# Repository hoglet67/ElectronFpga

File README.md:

# ElectronFpga

Inspired by [a thread on
Stardot](https://stardot.org.uk/forums/viewtopic.php?f=3&t=9223), this project
implements the Acorn Electron ULA in various FPGAs, and can emulate a full
Electron system on an FPGA eval board.

Features:
- Everything that was in the original Elk ULA (including cassette I/O)
- Turbo mode (memory access at 2MHz)
- JAFA Mode 7
- VGA output
- SD card access and MMFS

## Hardware targets

### Papilio Duo (Xilinx Spartan 6)

This can be used as a standalone Electron emulator, or with an adapter board
and some level shifters, as a ULA replacement.

### Altera DE1

This can be used as a standalone Electron emulator.

### Intel Max 10 (pcb/ folder in this repository)

This is a board designed specifically for this project, to fit inside an
Electron with its ULA replaced with turned-pin sockets.  Components:

- Intel Max 10 10M08SCU169 FPGA with 8k LUTs and 42kB block RAM.
- 32MB SDRAM
- 8+MB flash
- micro SD socket
- micro USB port
- stereo DAC for audio

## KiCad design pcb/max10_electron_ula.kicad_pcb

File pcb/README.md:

# ElectronFpga/pcb

This is a PCB for the Electron ULA replacement project (the "Ultimate Electron Upgrade").

Stardot thread:
https://stardot.org.uk/forums/viewtopic.php?f=3&t=9223

Status: v1 board sent to fab!

Pictures
--------

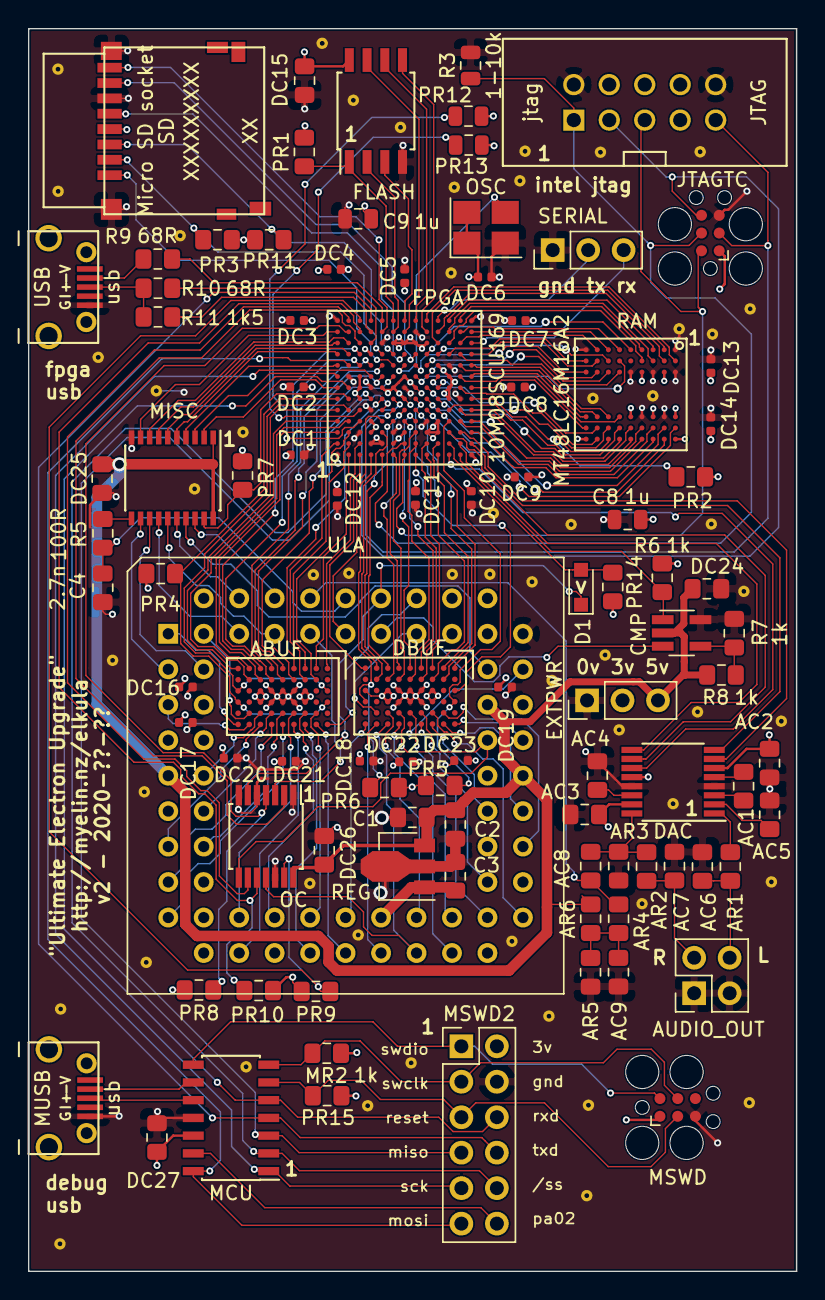
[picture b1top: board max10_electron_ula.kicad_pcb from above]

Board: 4 copper layers, 55.0 x 89.0 mm, 149 parts (0 on the bottom side), 194 nets.

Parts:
ABUF: 74LVTH162245ZRDR; ti_zrd_54_pbga
AC1, AC5: 1u; C_0805_2012Metric_Pad1.15x1.40mm_HandSolder
AC2, AC3: 4.7u; C_0805_2012Metric_Pad1.15x1.40mm_HandSolder
AC4: 2.2u; C_0805_2012Metric_Pad1.15x1.40mm_HandSolder
AC6, AC7: 2.7n NF; C_0805_2012Metric_Pad1.15x1.40mm_HandSolder
AC8, AC9: 10u; C_0805_2012Metric_Pad1.15x1.40mm_HandSolder
AR1, AR2: 560R NF; R_0805_2012Metric_Pad1.15x1.40mm_HandSolder
AR3: 10k NF; R_0805_2012Metric_Pad1.15x1.40mm_HandSolder
AR4, AR5, AR6: 10k; R_0805_2012Metric_Pad1.15x1.40mm_HandSolder
AUDIO_OUT: audio out; PinHeader_2x02_P2.54mm_Vertical
C1: 10u; C_0805_2012Metric_Pad1.15x1.40mm_HandSolder
C2, C3: 1u; C_0805_2012Metric_Pad1.15x1.40mm_HandSolder
C4: 2.7n; C_0805_2012Metric_Pad1.15x1.40mm_HandSolder
C8, C9: 1u; C_0805_2012Metric
CMP: MIC7221YM5-TR; SOT-23-5_HandSoldering
D1: BAT54; D_SOD-323_HandSoldering
DAC: WM8524CGEDT; TSSOP-16_4.4x5mm_P0.65mm
DBUF: 74LVTH162245ZRDR; ti_zrd_54_pbga
DC1, DC2, DC3, DC4, DC5, DC6, DC7, DC8, DC9, DC10, DC11, DC12, DC13, DC14, DC16, DC17, DC18, DC19, DC20, DC21, DC22, DC23: 100n; C_0402_1005Metric
DC15, DC24, DC25, DC26, DC27: 100n; C_0805_2012Metric_Pad1.15x1.40mm_HandSolder
EXTPWR: ext pwr; PinHeader_1x03_P2.54mm_Vertical
FLASH: W25Q128JVSIM; SOIJ-8_5.3x5.3mm_P1.27mm
FPGA: 10M08SCU169; intel_ubga169
JTAG: jtag; jtag_shrouded_2x5
JTAGTC: jtagtc; Tag-Connect_TC2030-IDC-FP_2x03_P1.27mm_Vertical
MCU: atsamd11c; SOIC-14_3.9x8.7mm_P1.27mm
MISC: 74HCT245PW; SSOP-20_4.4x6.5mm_P0.65mm
MR2: 1k; R_0805_2012Metric_Pad1.15x1.40mm_HandSolder
MSWD: swd; Tag-Connect_TC2030-IDC-FP_2x03_P1.27mm_Vertical
MSWD2: swd; PinHeader_2x06_P2.54mm_Vertical
MUSB: usb; micro_usb_b_smd_molex
OC: 74HCT125PW; TSSOP-14_4.4x5mm_P0.65mm
OSC: osc; Oscillator_SMD_Abracon_ASE-4Pin_3.2x2.5mm_HandSoldering
PR1, PR2, PR3, PR4, PR5, PR6, PR7, PR8, PR9, PR10, PR14, PR15: 10k; R_0805_2012Metric_Pad1.15x1.40mm_HandSolder
PR11: 10k NF; R_0805_2012Metric_Pad1.15x1.40mm_HandSolder
PR12, PR13: 10k; R_0805_2012Metric
R3: 1-10k; R_0805_2012Metric
R5: 100R; R_0805_2012Metric_Pad1.15x1.40mm_HandSolder
R6, R7, R8: 1k; R_0805_2012Metric_Pad1.15x1.40mm_HandSolder
R9, R10: 68R; R_0805_2012Metric_Pad1.15x1.40mm_HandSolder
R11: 1k5; R_0805_2012Metric_Pad1.15x1.40mm_HandSolder
RAM: MT48LC16M16A2; sdram_54tfbga
REG: AP7365-33YG-XX; SOT-89-3
SD: Micro SD socket; hirose_micro_sd_card_socket
SERIAL: fpga serial port; PinHeader_1x03_P2.54mm_Vertical
ULA: ULA header; PLCC-68_THT-Socket-Electron-ULA
USB: usb; micro_usb_b_smd_molex
staple_single1, staple_single2, staple_single3, staple_single4, staple_single5, staple_single6, staple_single7, staple_single8, staple_single9, staple_single10, staple_single11, staple_single12, staple_single13, staple_single14, staple_single15, staple_single16, staple_single17, staple_single18, staple_single19, staple_single20, staple_single21, staple_single22, staple_single23, staple_single24, staple_single25, staple_single26, staple_single27, staple_single28, staple_single29, staple_single30, staple_single31, staple_single32, staple_single33, staple_single34, staple_single35, staple_single36, staple_single37, staple_single38, staple_single39, staple_single40, staple_single41, staple_single42, staple_single43, staple_single44, staple_single45, staple_single46, staple_single47, staple_single48, staple_single49, staple_single50, staple_single51, staple_single52, staple_single53: via_single

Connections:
3V3: ABUF.C3, ABUF.C4, ABUF.G3, ABUF.G4, AC2.1, AC3.1, C3.1, C8.1, C9.1, DAC.6, DAC.12, DAC.15, DBUF.C3, DBUF.C4, DBUF.G3, DBUF.G4, DBUF.J3, DC1.1, DC2.1, DC3.1, DC4.1, DC5.1, DC6.1, DC7.1, DC8.1, DC9.1, DC10.1, DC11.1, DC12.1, DC13.1, DC14.1, DC15.1, DC16.2, DC17.2, DC18.2, DC19.2, DC20.2, DC21.2, DC22.2, DC23.2, DC27.2, EXTPWR.2, FLASH.8, FPGA.C6, FPGA.C7, FPGA.C8, FPGA.D3, FPGA.D4, FPGA.D10, FPGA.E7, FPGA.F2, FPGA.F7, FPGA.F11, FPGA.G3, FPGA.G6, FPGA.G8, FPGA.G11, FPGA.H7, FPGA.H11, FPGA.J3, FPGA.J11, FPGA.K3, FPGA.K4, FPGA.K9, FPGA.L6, FPGA.L7, FPGA.L8, JTAG.4, JTAGTC.1, MCU.12, MR2.2, MSWD.1, MSWD2.2, OSC.1, OSC.4, PR1.2, PR2.2, PR3.2, PR4.2, PR5.2, PR6.2, PR7.2, PR8.2, PR9.2, PR10.2, PR11.1, PR12.2, PR13.2, PR14.1, PR15.2, R6.2, RAM.A7, RAM.A9, RAM.B3, RAM.C7, RAM.D3, RAM.E7, RAM.J9, REG.1, SD.4, ULA.6, ULA.7, ULA.8, ULA.11, ULA.16, ULA.18, ULA.19, ULA.22, ULA.29, ULA.52, ULA.53
5V: AR6.2, C1.2, C2.2, CMP.2, DC24.2, DC25.2, DC26.1, EXTPWR.3, MISC.1, MISC.20, OC.14, R8.2, REG.3, ULA.9, ULA.43, ULA.48
A0_5V: ABUF.H6, ULA.5
A1_5V: ABUF.J6, ULA.1
A2_5V: ABUF.F5, ULA.12
A3_5V: ABUF.C6, ULA.24
A4_5V: ABUF.D5, ULA.21
A5_5V: ABUF.D6, ULA.20
A6_5V: ABUF.E6, ULA.17
A7_5V: ABUF.F6, ULA.15
A8_5V: ABUF.H5, ULA.2
A9_5V: ABUF.B6, ULA.26
A10_5V: ABUF.B5, ULA.25
A11_5V: ABUF.C5, ULA.23
A12_5V: ABUF.G6, ULA.13
A13_5V: ABUF.E5, ULA.14
A14_5V: ABUF.G5, ULA.10
A15_5V: ABUF.A6, ULA.56
A_buf_DIR: ABUF.A3, ABUF.J3, FPGA.B5
A_buf_nOE: ABUF.A4, ABUF.J4, FPGA.A6, PR4.1
CAPS_LOCK_5V: OC.3, ULA.63
CAS_IN_5V: CMP.3, ULA.59
CAS_IN_divider: CMP.4, R7.2, R8.1
CAS_MO_5V: MISC.18, ULA.64
CAS_OUT_5V: MISC.17, ULA.50
D_buf_DIR: DBUF.A3, FPGA.H1
D_buf_nOE: DBUF.A4, FPGA.L4, PR5.1
GND: ABUF.D3, ABUF.D4, ABUF.E3, ABUF.E4, ABUF.F3, ABUF.F4, AC1.2, AC2.2, AC3.2, AC4.2, AC6.2, AC7.2, AC9.2, AR3.2, AR5.2, AUDIO_OUT.1, AUDIO_OUT.3, C1.1, C2.1, C3.2, C4.2, C8.2, C9.2, CMP.5, DAC.4, DAC.13, DBUF.D3, DBUF.D4, DBUF.E3, DBUF.E4, DBUF.F3, DBUF.F4, DC1.2, DC2.2, DC3.2, DC4.2, DC5.2, DC6.2, DC7.2, DC8.2, DC9.2, DC10.2, DC11.2, DC12.2, DC13.2, DC14.2, DC15.2, DC16.1, DC17.1, DC18.1, DC19.1, DC20.1, DC21.1, DC22.1, DC23.1, DC24.1, DC25.1, DC26.2, DC27.1, EXTPWR.1, FLASH.4, FPGA.A1, FPGA.A13, FPGA.B8, FPGA.C3, FPGA.D2, FPGA.D5, FPGA.D7, FPGA.E2, FPGA.E11, FPGA.F3, FPGA.G7, FPGA.H12, FPGA.J4, FPGA.L9, FPGA.M6, FPGA.N1, FPGA.N13, JTAG.2, JTAG.10, JTAGTC.5, MCU.11, MISC.10, MSWD.5, MSWD2.4, MUSB.5, OC.1, OC.5, OC.7, OC.12, OSC.2, R3.2, R7.1, RAM.A1, RAM.A3, RAM.B7, RAM.C3, RAM.D7, RAM.E3, RAM.J1, REG.2, SD.6, SD.SH1, SD.SH2, SERIAL.1, ULA.51, ULA.68, USB.5, staple_single1.1, staple_single2.1, staple_single3.1, staple_single4.1, staple_single5.1, staple_single6.1, staple_single7.1, staple_single8.1, staple_single9.1, staple_single10.1, staple_single11.1, staple_single12.1, staple_single13.1, staple_single14.1, staple_single15.1, staple_single16.1, staple_single17.1, staple_single18.1, staple_single19.1, staple_single20.1, staple_single21.1, staple_single22.1, staple_single23.1, staple_single24.1, staple_single25.1, staple_single26.1, staple_single27.1, staple_single28.1, staple_single29.1, staple_single30.1, staple_single31.1, staple_single32.1, staple_single33.1, staple_single34.1, staple_single35.1, staple_single36.1, staple_single37.1, staple_single38.1, staple_single39.1, staple_single40.1, staple_single41.1, staple_single42.1, staple_single43.1, staple_single44.1, staple_single45.1, staple_single46.1, staple_single47.1, staple_single48.1, staple_single49.1, staple_single50.1, staple_single51.1, staple_single52.1, staple_single53.1
HS_n: FPGA.B10, MISC.6
IRQ_n_in: DBUF.G1, FPGA.E1
IRQ_n_out: FPGA.C13, OC.13, PR9.1
KBD0_5V: DBUF.J6, ULA.27
KBD1_5V: DBUF.H6, ULA.28
KBD2_5V: DBUF.G5, ULA.31
KBD3_5V: DBUF.F6, ULA.32
NMI_n_in: DBUF.H2, FPGA.F4
PD0_5V: DBUF.E5, ULA.33
PD1_5V: DBUF.C5, ULA.35
PD2_5V: DBUF.D6, ULA.36
PD3_5V: DBUF.D5, ULA.38
PD4_5V: DBUF.B5, ULA.39
PD5_5V: DBUF.B6, ULA.41
PD6_5V: DBUF.C6, ULA.42
PD7_5V: DBUF.A6, ULA.45
PHI_OUT_5V: C4.1, R5.2, ULA.60
PHI_OUT_5V_prefilter: MISC.11, R5.1
ROM_n: FPGA.E4, ULA.61
RST_n_in: D1.2, FPGA.L2, PR14.2
RST_n_out: FPGA.B12, OC.4, PR8.1
RnW_5V: DBUF.F5, OC.8, ULA.46
RnW_in: DBUF.F2, FPGA.H3
RnW_nOE: FPGA.C12, OC.10, PR10.1
RnW_out: FPGA.B13, OC.9
SOUND_OUT_5V: AC8.2, AR4.1, ULA.62
USBDM: R9.1, USB.2
USBDP: R10.1, R11.1, USB.3
USB_M: FPGA.E13, R9.2
USB_P: FPGA.D11, R10.2
USB_PU: FPGA.D12, R11.2
addr0: ABUF.H1, FPGA.B4
addr1: ABUF.J1, FPGA.A5
addr2: ABUF.F2, FPGA.C9
addr3: ABUF.C1, FPGA.B3
addr4: ABUF.D2, FPGA.F8
addr5: ABUF.D1, FPGA.E6
addr6: ABUF.E1, FPGA.E8
addr7: ABUF.F1, FPGA.D9
addr8: ABUF.H2, FPGA.A4
addr9: ABUF.B1, FPGA.B1
addr10: ABUF.B2, FPGA.B2
addr11: ABUF.C2, FPGA.A2
addr12: ABUF.G1, FPGA.C10
addr13: ABUF.E2, FPGA.E9
addr14: ABUF.G2, FPGA.A3
addr15: ABUF.A1, FPGA.C2
audio_bias: AC9.1, AR4.2, AR5.1, AR6.1
audio_out_left: AC6.1, AR1.2, AUDIO_OUT.4
audio_out_right: AC7.1, AR2.2, AUDIO_OUT.2
blue: FPGA.A9, MISC.4
blue_5V: MISC.16, ULA.66
caps: FPGA.C11, OC.2
casIn: CMP.1, FPGA.M1, R6.1
casMO: FPGA.A7, MISC.2
casOut: FPGA.A8, MISC.3
clk_in: DBUF.E1, FPGA.H4
clk_in_5V: DBUF.E6, ULA.49
clk_osc: FPGA.G9, OSC.3
clk_out: FPGA.A12, MISC.9
csync: FPGA.A10, MISC.5
csync_5V: MISC.15, ULA.65
dac_bclk: DAC.9, FPGA.M2
dac_dacdat: DAC.7, FPGA.M3
dac_lrclk: DAC.8, FPGA.N2
dac_mclk: DAC.10, FPGA.L3
dac_nmute: DAC.11, FPGA.L1
dac_out_left: AR1.1, DAC.1
dac_out_right: AC8.1, AR2.1, AR3.1, DAC.16
dac_power_cpca: AC5.1, DAC.5
dac_power_cpcb: AC5.2, DAC.3
dac_power_cpvoutn: AC1.1, DAC.2
dac_power_vmid: AC4.1, DAC.14
data0: DBUF.E2, FPGA.H2
data1: DBUF.C2, FPGA.H6
data2: DBUF.D1, FPGA.G4
data3: DBUF.D2, FPGA.J2
data4: DBUF.B2, FPGA.H5
data5: DBUF.B1, FPGA.K2
data6: DBUF.C1, FPGA.J1
data7: DBUF.A1, FPGA.K1
flash_IO0: FLASH.5, FPGA.J12
flash_IO1: FLASH.2, FPGA.F12
flash_IO2: FLASH.3, FPGA.G13
flash_IO3: FLASH.7, FPGA.G12
flash_SCK: FLASH.6, FPGA.H13
flash_nCE: FLASH.1, FPGA.F13, PR1.1
fpga_CONF_DONE: FPGA.C5, PR12.1
fpga_TCK: FPGA.G2, JTAG.1, JTAGTC.4, R3.1
fpga_TDI: FPGA.F5, JTAG.9, JTAGTC.3
fpga_TDO: FPGA.F6, JTAG.3, JTAGTC.6
fpga_TMS: FPGA.G1, JTAG.5, JTAGTC.2
fpga_nSTATUS: FPGA.C4, PR13.1
green: FPGA.A11, MISC.7
green_5V: MISC.13, ULA.4
input_buf_nOE: DBUF.J4, FPGA.D1, PR6.1
kbd0: DBUF.J1, FPGA.C1
kbd1: DBUF.H1, FPGA.E3
kbd2: DBUF.G2, FPGA.G5
kbd3: DBUF.F1, FPGA.F1
mcu_MISO: FPGA.E5, MCU.3, MSWD2.7
mcu_MOSI: FPGA.B9, MCU.14, MSWD2.11
mcu_PA02: MCU.13, MSWD2.12
mcu_RESET: MCU.6, MSWD.3, MSWD2.5, PR15.1
mcu_SCK: FPGA.D8, MCU.1, MSWD2.9
mcu_SS: FPGA.D6, MCU.2, MSWD2.10
mcu_SWCLK: MCU.7, MR2.1, MSWD.4, MSWD2.3
mcu_SWDIO: MCU.8, MSWD.2, MSWD2.1
mcu_USBDM: MCU.9, MUSB.2
mcu_USBDP: MCU.10, MUSB.3
mcu_debug_RXD: FPGA.B7, MCU.5, MSWD2.6
mcu_debug_TXD: FPGA.D13, MCU.4, MSWD2.8
misc_buf_nOE: FPGA.B6, MISC.19, PR7.1
nHS_5V: MISC.14, ULA.67
nIRQ_5V: DBUF.G6, OC.11, ULA.30
nNMI_5V: DBUF.H5, ULA.57
nRESET_5V: D1.1, OC.6, ULA.58
red: FPGA.B11, MISC.8
red_5V: MISC.12, ULA.3
sd_CLK_SCK: FPGA.G10, SD.5
sd_CMD_MOSI: FPGA.F10, PR11.2, SD.3
sd_DAT0_MISO: FPGA.H10, SD.7
sd_DAT1: FPGA.E12, SD.8
sd_DAT2: FPGA.F9, SD.1
sd_DAT3_nCS: FPGA.E10, PR3.1, SD.2
sdram_A0: FPGA.M9, RAM.H7
sdram_A1: FPGA.K7, RAM.H8
sdram_A2: FPGA.N7, RAM.J8
sdram_A3: FPGA.N8, RAM.J7
sdram_A4: FPGA.H9, RAM.J3
sdram_A5: FPGA.L10, RAM.J2
sdram_A6: FPGA.J9, RAM.H3
sdram_A7: FPGA.N10, RAM.H2
sdram_A8: FPGA.M11, RAM.H1
sdram_A9: FPGA.J8, RAM.G3
sdram_A10: FPGA.M7, RAM.H9
sdram_A11: FPGA.K10, RAM.G2
sdram_A12: FPGA.N12, RAM.G1
sdram_BA0: FPGA.N9, RAM.G7
sdram_BA1: FPGA.K8, RAM.G8
sdram_CKE: FPGA.M10, RAM.F3
sdram_CLK: FPGA.H8, RAM.F2
sdram_DQ0: FPGA.J5, RAM.A8
sdram_DQ1: FPGA.K5, RAM.B9
sdram_DQ2: FPGA.J6, RAM.B8
sdram_DQ3: FPGA.N3, RAM.C9
sdram_DQ4: FPGA.M4, RAM.C8
sdram_DQ5: FPGA.N4, RAM.D9
sdram_DQ6: FPGA.K6, RAM.D8
sdram_DQ7: FPGA.M5, RAM.E9
sdram_DQ8: FPGA.J10, RAM.E1
sdram_DQ9: FPGA.L11, RAM.D2
sdram_DQ10: FPGA.M13, RAM.D1
sdram_DQ11: FPGA.L12, RAM.C2
sdram_DQ12: FPGA.L13, RAM.C1
sdram_DQ13: FPGA.K12, RAM.B2
sdram_DQ14: FPGA.K11, RAM.B1
sdram_DQ15: FPGA.J13, RAM.A2
sdram_LDQM: FPGA.N5, RAM.E8
sdram_UDQM: FPGA.M12, RAM.F1
sdram_nCAS: FPGA.M8, RAM.F7
sdram_nCS: FPGA.N6, PR2.1, RAM.G9
sdram_nRAS: FPGA.L5, RAM.F8
sdram_nWE: FPGA.J7, RAM.F9
serial_RXD: FPGA.N11, SERIAL.3
serial_TXD: FPGA.K13, SERIAL.2

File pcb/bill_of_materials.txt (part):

Identifier	Value	Description	KiCad package
DC1	100n	Capacitor 0402: 100n	Capacitor_SMD:C_0402_1005Metric
DC10	100n	Capacitor 0402: 100n	Capacitor_SMD:C_0402_1005Metric
DC11	100n	Capacitor 0402: 100n	Capacitor_SMD:C_0402_1005Metric
DC12	100n	Capacitor 0402: 100n	Capacitor_SMD:C_0402_1005Metric
DC13	100n	Capacitor 0402: 100n	Capacitor_SMD:C_0402_1005Metric
DC14	100n	Capacitor 0402: 100n	Capacitor_SMD:C_0402_1005Metric
DC16	100n	Capacitor 0402: 100n	Capacitor_SMD:C_0402_1005Metric
DC17	100n	Capacitor 0402: 100n	Capacitor_SMD:C_0402_1005Metric
DC18	100n	Capacitor 0402: 100n	Capacitor_SMD:C_0402_1005Metric
DC19	100n	Capacitor 0402: 100n	Capacitor_SMD:C_0402_1005Metric
DC2	100n	Capacitor 0402: 100n	Capacitor_SMD:C_0402_1005Metric
DC20	100n	Capacitor 0402: 100n	Capacitor_SMD:C_0402_1005Metric
DC21	100n	Capacitor 0402: 100n	Capacitor_SMD:C_0402_1005Metric
DC22	100n	Capacitor 0402: 100n	Capacitor_SMD:C_0402_1005Metric
DC23	100n	Capacitor 0402: 100n	Capacitor_SMD:C_0402_1005Metric
DC3	100n	Capacitor 0402: 100n	Capacitor_SMD:C_0402_1005Metric
DC4	100n	Capacitor 0402: 100n	Capacitor_SMD:C_0402_1005Metric
DC5	100n	Capacitor 0402: 100n	Capacitor_SMD:C_0402_1005Metric
DC6	100n	Capacitor 0402: 100n	Capacitor_SMD:C_0402_1005Metric
DC7	100n	Capacitor 0402: 100n	Capacitor_SMD:C_0402_1005Metric
DC8	100n	Capacitor 0402: 100n	Capacitor_SMD:C_0402_1005Metric
DC9	100n	Capacitor 0402: 100n	Capacitor_SMD:C_0402_1005Metric
DC15	100n	Capacitor 0805: 100n	Capacitor_SMD:C_0805_2012Metric_Pad1.15x1.40mm_HandSolder
DC24	100n	Capacitor 0805: 100n	Capacitor_SMD:C_0805_2012Metric_Pad1.15x1.40mm_HandSolder
DC25	100n	Capacitor 0805: 100n	Capacitor_SMD:C_0805_2012Metric_Pad1.15x1.40mm_HandSolder
DC26	100n	Capacitor 0805: 100n	Capacitor_SMD:C_0805_2012Metric_Pad1.15x1.40mm_HandSolder
DC27	100n	Capacitor 0805: 100n	Capacitor_SMD:C_0805_2012Metric_Pad1.15x1.40mm_HandSolder
AC8	10u	Capacitor 0805: 10u	Capacitor_SMD:C_0805_2012Metric_Pad1.15x1.40mm_HandSolder
AC9	10u	Capacitor 0805: 10u	Capacitor_SMD:C_0805_2012Metric_Pad1.15x1.40mm_HandSolder
C1	10u	Capacitor 0805: 10u	Capacitor_SMD:C_0805_2012Metric_Pad1.15x1.40mm_HandSolder
AC1	1u	Capacitor 0805: 1u	Capacitor_SMD:C_0805_2012Metric_Pad1.15x1.40mm_HandSolder
AC5	1u	Capacitor 0805: 1u	Capacitor_SMD:C_0805_2012Metric_Pad1.15x1.40mm_HandSolder
C2	1u	Capacitor 0805: 1u	Capacitor_SMD:C_0805_2012Metric_Pad1.15x1.40mm_HandSolder
C3	1u	Capacitor 0805: 1u	Capacitor_SMD:C_0805_2012Metric_Pad1.15x1.40mm_HandSolder
C8	1u	Capacitor 0805: 1u	Capacitor_SMD:C_0805_2012Metric
C9	1u	Capacitor 0805: 1u	Capacitor_SMD:C_0805_2012Metric
AC4	2.2u	Capacitor 0805: 2.2u	Capacitor_SMD:C_0805_2012Metric_Pad1.15x1.40mm_HandSolder
C4	2.7n	Capacitor 0805: 2.7n	Capacitor_SMD:C_0805_2012Metric_Pad1.15x1.40mm_HandSolder
AC6	2.7n NF	Capacitor 0805: 2.7n NF	Capacitor_SMD:C_0805_2012Metric_Pad1.15x1.40mm_HandSolder
AC7	2.7n NF	Capacitor 0805: 2.7n NF	Capacitor_SMD:C_0805_2012Metric_Pad1.15x1.40mm_HandSolder
AC2	4.7u	Capacitor 0805: 4.7u	Capacitor_SMD:C_0805_2012Metric_Pad1.15x1.40mm_HandSolder
AC3	4.7u	Capacitor 0805: 4.7u	Capacitor_SMD:C_0805_2012Metric_Pad1.15x1.40mm_HandSolder
D1	BAT54	Diode SOD323: BAT54	Diode_SMD:D_SOD-323_HandSoldering
FLASH	W25Q128JVSIM	IC 128Mbit QSPI flash; https://www.digikey.com/product-detail/en/winbond-electronic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	Package_SO:SOIJ-8_5.3x5.3mm_P1.27mm
MCU	atsamd11c	IC ARM MCU; https://www.digikey.com/product-detail/en/microchip-technolo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	Package_SO:SOIC-14_3.9x8.7mm_P1.27mm
DAC	WM8524CGEDT	IC Audio DAC; https://www.digikey.com/product-detail/en/cirrus-logic-inc/W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	Package_SO:TSSOP-16_4.4x5mm_P0.65mm
CMP	MIC7221YM5-TR	IC Comparator; https://www.digikey.com/product-detail/en/microchip-technolo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	Package_TO_SOT_SMD:SOT-23-5_HandSoldering
FPGA	10M08SCU169	IC FPGA Intel Max 10; https://www.digikey.com/product-detail/en/10M08SCU169C8G/544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	myelin-kicad:intel_ubga169
REG	AP7365-33YG-XX	IC LDO 3.3V regulator; https://www.digikey.com/products/en?keywords=AP7365-33YG-13DICT-ND	Package_TO_SOT_SMD:SOT-89-3
RAM	MT48LC16M16A2	IC SDRAM 32MB; MT48LC16M16A2F4-6A:GTR	myelin-kicad:sdram_54tfbga
ABUF	74LVTH162245ZRDR	IC buffer 16-bit; https://www.digikey.com/product-detail/en/texas-instruments/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	myelin-kicad:ti_zrd_54_pbga
DBUF	74LVTH162245ZRDR	IC buffer 16-bit; https://www.digikey.com/product-detail/en/texas-instruments/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	myelin-kicad:ti_zrd_54_pbga
OC	74HCT125PW	IC buffer 4-bit OC; https://www.digikey.com/product-detail/en/nexperia-usa-inc/7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	Package_SO:TSSOP-14_4.4x5mm_P0.65mm
MISC	74HCT245PW	IC buffer 8-bit; https://www.digikey.com/product-detail/en/nexperia-usa-inc/7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	Package_SO:SSOP-20_4.4x6.5mm_P0.65mm
OSC	osc	IC oscillator 16MHz; https://www.digikey.com/product-detail/en/microchip-technolo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	Oscillator:Oscillator_SMD_Abracon_ASE-4Pin_3.2x2.5mm_HandSoldering
AUDIO_OUT	audio out	Pin header	Connector_PinHeader_2.54mm:PinHeader_2x02_P2.54mm_Vertical
SERIAL	fpga serial port	Pin header	Connector_PinHeader_2.54mm:PinHeader_1x03_P2.54mm_Vertical
JTAG	jtag	Pin header	myelin-kicad:jtag_shrouded_2x5
MSWD2	swd	Pin header	Connector_PinHeader_2.54mm:PinHeader_2x06_P2.54mm_Vertical
EXTPWR	ext pwr	Pin header - 1x3 0.1 inch male	Connector_PinHeader_2.54mm:PinHeader_1x03_P2.54mm_Vertical
ULA	ULA header	Pin header - round - to plug into an Acorn Electron ULA socket	modified-kicad:PLCC-68_THT-Socket-Electron-ULA
R3	1-10k	Resistor 0805: 1-10k	Resistor_SMD:R_0805_2012Metric
R5	100R	Resistor 0805: 100R	Resistor_SMD:R_0805_2012Metric_Pad1.15x1.40mm_HandSolder
AR4	10k	Resistor 0805: 10k	Resistor_SMD:R_0805_2012Metric_Pad1.15x1.40mm_HandSolder
AR5	10k	Resistor 0805: 10k	Resistor_SMD:R_0805_2012Metric_Pad1.15x1.40mm_HandSolder
AR6	10k	Resistor 0805: 10k	Resistor_SMD:R_0805_2012Metric_Pad1.15x1.40mm_HandSolder
PR1	10k	Resistor 0805: 10k	Resistor_SMD:R_0805_2012Metric_Pad1.15x1.40mm_HandSolder
PR10	10k	Resistor 0805: 10k	Resistor_SMD:R_0805_2012Metric_Pad1.15x1.40mm_HandSolder
PR12	10k	Resistor 0805: 10k	Resistor_SMD:R_0805_2012Metric
PR13	10k	Resistor 0805: 10k	Resistor_SMD:R_0805_2012Metric
PR14	10k	Resistor 0805: 10k	Resistor_SMD:R_0805_2012Metric_Pad1.15x1.40mm_HandSolder
PR15	10k	Resistor 0805: 10k	Resistor_SMD:R_0805_2012Metric_Pad1.15x1.40mm_HandSolder
PR2	10k	Resistor 0805: 10k	Resistor_SMD:R_0805_2012Metric_Pad1.15x1.40mm_HandSolder
PR3	10k	Resistor 0805: 10k	Resistor_SMD:R_0805_2012Metric_Pad1.15x1.40mm_HandSolder
PR4	10k	Resistor 0805: 10k	Resistor_SMD:R_0805_2012Metric_Pad1.15x1.40mm_HandSolder
PR5	10k	Resistor 0805: 10k	Resistor_SMD:R_0805_2012Metric_Pad1.15x1.40mm_HandSolder
PR6	10k	Resistor 0805: 10k	Resistor_SMD:R_0805_2012Metric_Pad1.15x1.40mm_HandSolder
PR7	10k	Resistor 0805: 10k	Resistor_SMD:R_0805_2012Metric_Pad1.15x1.40mm_HandSolder
PR8	10k	Resistor 0805: 10k	Resistor_SMD:R_0805_2012Metric_Pad1.15x1.40mm_HandSolder
PR9	10k	Resistor 0805: 10k	Resistor_SMD:R_0805_2012Metric_Pad1.15x1.40mm_HandSolder
AR3	10k NF	Resistor 0805: 10k NF	Resistor_SMD:R_0805_2012Metric_Pad1.15x1.40mm_HandSolder
PR11	10k NF	Resistor 0805: 10k NF	Resistor_SMD:R_0805_2012Metric_Pad1.15x1.40mm_HandSolder
MR2	1k	Resistor 0805: 1k	Resistor_SMD:R_0805_2012Metric_Pad1.15x1.40mm_HandSolder
R6	1k	Resistor 0805: 1k	Resistor_SMD:R_0805_2012Metric_Pad1.15x1.40mm_HandSolder
R7	1k	Resistor 0805: 1k	Resistor_SMD:R_0805_2012Metric_Pad1.15x1.40mm_HandSolder
R8	1k	Resistor 0805: 1k	Resistor_SMD:R_0805_2012Metric_Pad1.15x1.40mm_HandSolder
R11	1k5	Resistor 0805: 1k5	Resistor_SMD:R_0805_2012Metric_Pad1.15x1.40mm_HandSolder
AR1	560R NF	Resistor 0805: 560R NF	Resistor_SMD:R_0805_2012Metric_Pad1.15x1.40mm_HandSolder
AR2	560R NF	Resistor 0805: 560R NF	Resistor_SMD:R_0805_2012Metric_Pad1.15x1.40mm_HandSolder
R10	68R	Resistor 0805: 68R	Resistor_SMD:R_0805_2012Metric_Pad1.15x1.40mm_HandSolder
R9	68R	Resistor 0805: 68R	Resistor_SMD:R_0805_2012Metric_Pad1.15x1.40mm_HandSolder
MUSB	usb	Socket Micro USB, Molex 1050170001; https://www.digikey.com/products/en?keywords=WM1399CT-ND	myelin-kicad:micro_usb_b_smd_molex
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
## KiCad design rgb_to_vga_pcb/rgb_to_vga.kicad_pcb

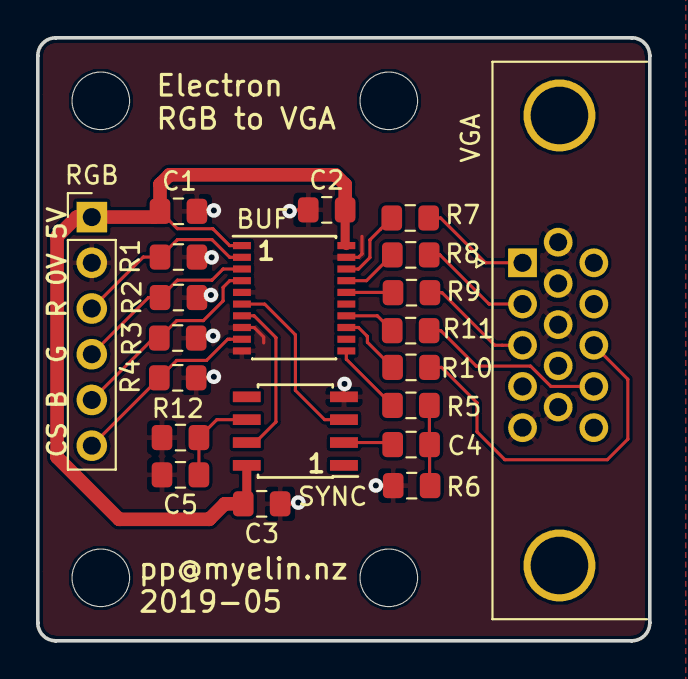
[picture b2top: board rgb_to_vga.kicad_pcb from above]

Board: 2 copper layers, 34.0 x 33.5 mm, 21 parts (0 on the bottom side), 22 nets.

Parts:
BUF: 74HCT245PW; SSOP-20_4.4x6.5mm_P0.65mm
C1: 10u; C_0805_2012Metric_Pad1.15x1.40mm_HandSolder
C2, C3, C4, C5: 100n; C_0805_2012Metric_Pad1.15x1.40mm_HandSolder
R1, R2, R3, R4: 10k NF; R_0805_2012Metric_Pad1.15x1.40mm_HandSolder
R5: 4k TBD; R_0805_2012Metric_Pad1.15x1.40mm_HandSolder
R6: 1k TBD; R_0805_2012Metric_Pad1.15x1.40mm_HandSolder
R7, R8, R9: 480R; R_0805_2012Metric_Pad1.15x1.40mm_HandSolder
R10, R11: 100R; R_0805_2012Metric_Pad1.15x1.40mm_HandSolder
R12: 681k 1%; R_0805_2012Metric_Pad1.15x1.40mm_HandSolder
RGB: RGB; PinHeader_1x06_P2.54mm_Vertical
SYNC: EL1883; SOIC-8_3.9x4.9mm_P1.27mm
VGA: VGA; DSUB-15-HD_Female_Horizontal_P2.29x1.98mm_EdgePinOffset3.03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

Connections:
5V: BUF.1, BUF.20, C1.2, C2.2, C3.2, RGB.1, SYNC.8
B_buf: BUF.16, R9.1
B_in: BUF.4, R3.1, RGB.5
B_out: R9.2, VGA.3
CS_buf: BUF.11, R5.1
CS_coupled: C4.2, SYNC.2
CS_divided: C4.1, R5.2, R6.1
CS_in: BUF.9, R4.1, RGB.6
GND: BUF.5, BUF.8, BUF.10, BUF.19, C1.1, C2.1, C3.1, C5.2, R1.2, R2.2, R3.2, R4.2, R6.2, R12.2, RGB.2, SYNC.4, VGA.5, VGA.6, VGA.7, VGA.8, VGA.10
G_buf: BUF.17, R8.1
G_in: BUF.3, R2.1, RGB.4
G_out: R8.2, VGA.2
HS: BUF.7, SYNC.7
HS_buf: BUF.13, R10.1
HS_out: R10.2, VGA.13
RSET: C5.1, R12.1, SYNC.6
R_buf: BUF.18, R7.1
R_in: BUF.2, R1.1, RGB.3
R_out: R7.2, VGA.1
VS: BUF.6, SYNC.3
VS_buf: BUF.14, R11.1
VS_out: R11.2, VGA.14

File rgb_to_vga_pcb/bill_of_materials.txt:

Identifier	Value	Description	KiCad package
BUF	74HCT245PW	https://www.digikey.com/product-detail/en/nexperia-usa-inc/7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	Package_SO:SSOP-20_4.4x6.5mm_P0.65mm
C1	10u	10u capacitor in 0805 package	Capacitor_SMD:C_0805_2012Metric_Pad1.15x1.40mm_HandSolder
C2	100n	100n capacitor in 0805 package	Capacitor_SMD:C_0805_2012Metric_Pad1.15x1.40mm_HandSolder
C3	100n	100n capacitor in 0805 package	Capacitor_SMD:C_0805_2012Metric_Pad1.15x1.40mm_HandSolder
C4	100n	100n capacitor in 0805 package	Capacitor_SMD:C_0805_2012Metric_Pad1.15x1.40mm_HandSolder
C5	100n	100n capacitor in 0805 package	Capacitor_SMD:C_0805_2012Metric_Pad1.15x1.40mm_HandSolder
R1	10k NF	10k NF resistor in 0805 package	Resistor_SMD:R_0805_2012Metric_Pad1.15x1.40mm_HandSolder
R10	100R	100R resistor in 0805 package	Resistor_SMD:R_0805_2012Metric_Pad1.15x1.40mm_HandSolder
R11	100R	100R resistor in 0805 package	Resistor_SMD:R_0805_2012Metric_Pad1.15x1.40mm_HandSolder
R12	681k 1%	681k 1% resistor in 0805 package	Resistor_SMD:R_0805_2012Metric_Pad1.15x1.40mm_HandSolder
R2	10k NF	10k NF resistor in 0805 package	Resistor_SMD:R_0805_2012Metric_Pad1.15x1.40mm_HandSolder
R3	10k NF	10k NF resistor in 0805 package	Resistor_SMD:R_0805_2012Metric_Pad1.15x1.40mm_HandSolder
R4	10k NF	10k NF resistor in 0805 package	Resistor_SMD:R_0805_2012Metric_Pad1.15x1.40mm_HandSolder
R5	4k TBD	4k TBD resistor in 0805 package	Resistor_SMD:R_0805_2012Metric_Pad1.15x1.40mm_HandSolder
R6	1k TBD	1k TBD resistor in 0805 package	Resistor_SMD:R_0805_2012Metric_Pad1.15x1.40mm_HandSolder
R7	480R	480R resistor in 0805 package	Resistor_SMD:R_0805_2012Metric_Pad1.15x1.40mm_HandSolder
R8	480R	480R resistor in 0805 package	Resistor_SMD:R_0805_2012Metric_Pad1.15x1.40mm_HandSolder
R9	480R	480R resistor in 0805 package	Resistor_SMD:R_0805_2012Metric_Pad1.15x1.40mm_HandSolder
RGB	RGB		Connector_PinHeader_2.54mm:PinHeader_1x06_P2.54mm_Vertical
SYNC	EL1883		Package_SO:SOIC-8_3.9x4.9mm_P1.27mm
VGA	VGA		Connector_Dsub:DSUB-15-HD_Female_Horizontal_P2.29x1.98mm_EdgePinOffset3.03mm_Housed_MountingHolesOffset4.94mm

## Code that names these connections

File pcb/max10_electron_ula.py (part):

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
        # Keyboard: KBD0-3 are 5V inputs, driven by CPU address lines.
        # CAPS_LOCK is an OC output (low speed).
        Pin(27, "KBD0",      "KBD0_5V"),  # I (LVT buf)
        Pin(28, "KBD1",      "KBD1_5V"),  # I (LVT buf)
        Pin(31, "KBD2",      "KBD2_5V"),  # I (LVT buf)
        Pin(32, "KBD3",      "KBD3_5V"),  # I (LVT buf)
        Pin(63, "CAPS_LOCK", "CAPS_LOCK_5V"),  # O (HCT125 OC), drives caps LED via 470R (~6mA)

        # nRST is apparently an input, but being able to drive it seems sensible.
        Pin(58, "nRST", "nRESET_5V"),  # OC I (diode/resistor buf + HCT125 OC)

        # nROM is the TTL ROM chip select, so doesn't need a buffer.
        Pin(61, "nROM", "ROM_n"),    # O (direct output from FPGA)

        # Address bus: input; use 74lvth162245 with A-port (with 22R series
        # resistors) connected to Electron.
        Pin( 5, "A0",  "A0_5V"),   # IO (LVT buf, reversible)
        Pin( 1, "A1",  "A1_5V"),   # IO (LVT buf, reversible)
        Pin(12, "A2",  "A2_5V"),   # IO (LVT buf, reversible)
        Pin(24, "A3",  "A3_5V"),   # IO (LVT buf, reversible)
        Pin(21, "A4",  "A4_5V"),   # IO (LVT buf, reversible)
        Pin(20, "A5",  "A5_5V"),   # IO (LVT buf, reversible)
        Pin(17, "A6",  "A6_5V"),   # IO (LVT buf, reversible)
        Pin(15, "A7",  "A7_5V"),   # IO (LVT buf, reversible)
        Pin( 2, "A8",  "A8_5V"),   # IO (LVT buf, reversible)
        Pin(26, "A9",  "A9_5V"),   # IO (LVT buf, reversible)
        Pin(25, "A10", "A10_5V"),  # IO (LVT buf, reversible)
        Pin(23, "A11", "A11_5V"),  # IO (LVT buf, reversible)
        Pin(13, "A12", "A12_5V"),  # IO (LVT buf, reversible)
        Pin(14, "A13", "A13_5V"),  # IO (LVT buf, reversible)
        Pin(10, "A14", "A14_5V"),  # IO (LVT buf, reversible)
        Pin(56, "A15", "A15_5V"),  # IO (LVT buf, reversible)

        # Data bus: input/output
        Pin(33, "PD0", "PD0_5V"),  # IO (LVT buf, bidirectional)
        Pin(35, "PD1", "PD1_5V"),  # IO (LVT buf, bidirectional)
        Pin(36, "PD2", "PD2_5V"),  # IO (LVT buf, bidirectional)
        Pin(38, "PD3", "PD3_5V"),  # IO (LVT buf, bidirectional)
        Pin(39, "PD4", "PD4_5V"),  # IO (LVT buf, bidirectional)
        Pin(41, "PD5", "PD5_5V"),  # IO (LVT buf, bidirectional)
        Pin(42, "PD6", "PD6_5V"),  # IO (LVT buf, bidirectional)
        Pin(45, "PD7", "PD7_5V"),  # IO (LVT buf, bidirectional)

        # nNMI is an input to the ULA and CPU.
        Pin(57, "nNMI",    "nNMI_5V"),     # I (LVT buf) (OC externally but not for us)
        # PHI_OUT is a 5V signal with CMOS levels.
        Pin(60, "PHI_OUT", "PHI_OUT_5V"),  # O (HCT245 out)
        # nIRQ is an output from the ULA, input to the CPU.
        Pin(30, "nIRQ",    "nIRQ_5V"),     # OC IO (LVT buf + HCT125 OC)
        # RnW is an input to the ULA, output from the CPU.
        Pin(46, "RnW",     "RnW_5V"),      # IO (LVT buf + HCT125 optional out)

        # Clocks and ground
        Pin(55, "DIV13_IN"),                  # NC - unused by FPGA
        Pin(68, "GND", "GND"),
        Pin(51, "GND", "GND"),
        Pin(49, "CLOCK_IN", "clk_in_5V"),  # I (LVT buf)

        # Video: direct from FPGA ok as all go straight to buffers
        Pin(67, "nHS",    "nHS_5V"),     # O (HCT245 out) - horizontal sync
        Pin( 3, "red",    "red_5V"),     # O (HCT245 out)
        Pin( 4, "green",  "green_5V"),   # O (HCT245 out)
        Pin(66, "blue",   "blue_5V"),    # O (HCT245 out)
        Pin(65, "csync",  "csync_5V"),  # O (HCT245 out) - composite sync

        # Power-on reset
        Pin(54, "nPOR"),  # NC - FPGA already has power on detect

        # Audio
        Pin(62, "SOUND_OUT", "SOUND_OUT_5V"),  # O (via WM8524 DAC), goes straight to amplifier

        # Cassettte
        Pin(59, "CAS_IN",  "CAS_IN_5V"),   # I (via MIC7221 comparator)
        Pin(64, "CAS_MO",  "CAS_MO_5V"),   # O (HCT245 out) - motor relay (2mA)
        Pin(50, "CAS_OUT", "CAS_OUT_5V"),  # O (HCT245 out)
        Pin(47, "CAS_RC"),                 # NC - cassette high tone detect

        # Power
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            Pin("B6",  "",         "NEXT_CONN"),
            Pin("F8",  "",         "NEXT_CONN"),
            Pin("A7",  "",         "NEXT_CONN"),
            Pin("B7",  "VREFB8N0", "mcu_debug_RXD"),
            Pin("A8",  "",         "NEXT_CONN"),
            Pin("E8",  "",         "NEXT_CONN"),
            Pin("E9",  "",         "NEXT_CONN"),
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            Pin("C12", "",         "NEXT_CONN"),
            Pin("C13", "",         "NEXT_CONN"),
            Pin("D12", "",         "NEXT_CONN"),
            Pin("D13", "VREFB6N0", "mcu_debug_TXD"),
            Pin("F9",  "DPCLK3",   "NEXT_CONN"),
            Pin("E10", "",         "NEXT_CONN"),
            Pin("F10", "DPCLK2",   "NEXT_CONN"),
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            Pin("E13", "CLK3n",    "NEXT_CONN"),
            Pin("E12", "",         "NEXT_CONN"),
            Pin("F13", "CLK3p",    "NEXT_CONN"),
            Pin("G9",  "CLK2p",    "clk_osc"),
            Pin("F12", "",         "NEXT_CONN"),
            Pin("G13", "",         "NEXT_CONN"),
            Pin("G10", "CLK2n",    "NEXT_CONN"),
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            Pin("J12", "",         "NEXT_CONN"),
            Pin("J13", "",         "NEXT_CONN"),
            Pin("K11", "",         "NEXT_CONN"),
            Pin("K13", "VREFB5N0", "serial_TXD"),
            Pin("K12", "",         "NEXT_CONN"),
            Pin("J10", "",         "NEXT_CONN"),
            Pin("L12", "",         "NEXT_CONN"),
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            Pin("M12", "",         "NEXT_CONN"),
            Pin("N12", "",         "NEXT_CONN"),
            Pin("M11", "",         "NEXT_CONN"),
            Pin("N11", "VREFB3N0", "serial_RXD"),
            Pin("L10", "",         "NEXT_CONN"),
            Pin("H9",  "",         "NEXT_CONN"),
            Pin("N10", "",         "NEXT_CONN"),
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            Pin("M2",  "",         "NEXT_CONN"),
            Pin("M1",  "",         "NEXT_CONN"),
            Pin("L2",  "",         "NEXT_CONN"),
            Pin("L1",  "VREFB2N0", "dac_nmute"),
            Pin("L4",  "",         "NEXT_CONN"),
            Pin("K1",  "",         "NEXT_CONN"),
            Pin("K2",  "",         "NEXT_CONN"),
            Pin("H5",  "CLK1n",    "NEXT_CONN"),
            Pin("J1",  "",         "NEXT_CONN"),
            Pin("J2",  "",         "NEXT_CONN"),
            Pin("H1",  "VREFB1N0", "D_buf_DIR"),
            Pin("G4",  "",         "NEXT_CONN"),
            Pin("H6",  "CLK0p",    "NEXT_CONN"),
            Pin("H4",  "CLK1p",    "clk_in"),
            Pin("H2",  "",         "NEXT_CONN"),
            Pin("H3",  "",         "NEXT_CONN"),
            Pin("F1",  "",         "NEXT_CONN"),
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
            # 12 JTAG and other special pins
            # These are IO by default unless enabled in Assignments > Device
            Pin("B9",  "DEV_CLRn",   "mcu_MOSI"),
            Pin("D8",  "DEV_OE",     "mcu_SCK"),
            Pin("E5",  "JTAGEN",     "mcu_MISO"),
            Pin("D6",  "CRC_ERROR",  "mcu_SS"),

            # These are reserved by the fitter by default -- leave them alone
            Pin("C4",  "nSTATUS",    "fpga_nSTATUS"),  # MUST be pulled high during init
            Pin("C5",  "CONF_DONE",  "fpga_CONF_DONE"),  # MUST be pulled high during init
            Pin("D7",  "CONFIG_SEL", "GND"),  # unused, so connected to GND
            Pin("E7",  "nCONFIG",    "3V3"),  # can be connected straight to VCCIO
            Pin("F5",  "TDI",        "fpga_TDI"),
            Pin("F6",  "TDO",        "fpga_TDO"),
            Pin("G1",  "TMS",        "fpga_TMS"),
            Pin("G2",  "TCK",        "fpga_TCK"),

            # 39 power and ground pins
            Pin("D2",  "GND",     "GND"),
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Pin("F1", "", "io_b1A_L7n_F1"),
Pin("E1", "", "io_b1A_L7p_E1"),
Pin("E5", "", "fpga_JTAGEN"),
Pin("G1", "", "fpga_TMS"),
Pin("H1", "", "special_VREFB1N0_nodiff_H1"),
Pin("G2", "", "fpga_TCK"),
Pin("F5", "", "fpga_TDI"),
Pin("F6", "", "fpga_TDO"),
Pin("F4", "", "io_b1B_L14n_F4"),
Pin("G4", "", "io_b1B_L14p_G4"),
Pin("H2", "", "io_b1B_L16n_H2"),
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Pin("B3", "", "io_b8_T23p_B3"),
Pin("D6", "", "fpga_CRC_ERROR"),
Pin("B4", "", "io_b8_T23n_B4"),
Pin("C4", "", "fpga_nSTATUS"),
Pin("A5", "", "singleended_unknown_b8_A5"),
Pin("C5", "", "fpga_CONF_DONE"),
Pin("A2", "", "io_b8_T26p_A2"),
Pin("B2", "", "io_b8_T26n_B2"),
Pin("D2", "", "GND"),
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    value="jtag",
    desc="Pin header",
    pins=[
        Pin( 1, "TCK", "fpga_TCK"), # top left
        Pin( 2, "GND", "GND"), # top right
        Pin( 3, "TDO", "fpga_TDO"),
        Pin( 4, "3V3", "3V3"),
        Pin( 5, "TMS", "fpga_TMS"),
        Pin( 6, "NC"),
        Pin( 7, "NC"),
        Pin( 8, "NC"),
        Pin( 9, "TDI", "fpga_TDI"),
        Pin(10, "GND", "GND"),
    ],
)
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        # which will then work with the TC2030-CTX.

        Pin(1, "VCC", "3V3"),       # Cortex pin 1
        Pin(2, "TMS", "fpga_TMS"),  # Cortex pin 2 (SWDIO)
        Pin(3, "TDI", "fpga_TDI"),  # Cortex pin 10 (nRESET)
        Pin(4, "TCK", "fpga_TCK"),  # Cortex pin 4 (SWCLK)
        Pin(5, "GND", "GND"),       # Cortex pin 3, 5, 9
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
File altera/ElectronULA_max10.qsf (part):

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set_location_assignment PIN_B4 -to addr[0]
set_location_assignment PIN_A4 -to addr[8]
set_location_assignment PIN_A5 -to addr[1]
set_location_assignment PIN_B5 -to A_buf_DIR
set_location_assignment PIN_E6 -to addr[5]
set_location_assignment PIN_A6 -to A_buf_nOE
set_location_assignment PIN_B6 -to misc_buf_nOE
set_location_assignment PIN_F8 -to addr[4]
set_location_assignment PIN_A7 -to casMO
set_location_assignment PIN_B7 -to mcu_debug_RXD
set_location_assignment PIN_A8 -to casOut
set_location_assignment PIN_E8 -to addr[6]
set_location_assignment PIN_E9 -to addr[13]
set_location_assignment PIN_D9 -to addr[7]
set_location_assignment PIN_A9 -to blue
set_location_assignment PIN_C9 -to addr[2]
set_location_assignment PIN_A10 -to csync
set_location_assignment PIN_B10 -to HS_n
set_location_assignment PIN_C10 -to addr[12]
set_location_assignment PIN_A11 -to green
set_location_assignment PIN_B11 -to red
set_location_assignment PIN_A12 -to clk_out
set_location_assignment PIN_B12 -to RST_n_out
set_location_assignment PIN_C11 -to caps
set_location_assignment PIN_B13 -to RnW_out
set_location_assignment PIN_C12 -to RnW_nOE
set_location_assignment PIN_C13 -to IRQ_n_out
set_location_assignment PIN_D12 -to USB_PU
set_location_assignment PIN_D13 -to mcu_debug_TXD
set_location_assignment PIN_F9 -to sd_DAT2
set_location_assignment PIN_E10 -to sd_DAT3_nCS
set_location_assignment PIN_F10 -to sd_CMD_MOSI
set_location_assignment PIN_D11 -to USB_P
set_location_assignment PIN_E13 -to USB_M
set_location_assignment PIN_E12 -to sd_DAT1
set_location_assignment PIN_F13 -to flash_nCE
set_location_assignment PIN_G9 -to clk_osc
set_location_assignment PIN_F12 -to flash_IO1
set_location_assignment PIN_G13 -to flash_IO2
set_location_assignment PIN_G10 -to sd_CLK_SCK
set_location_assignment PIN_G12 -to flash_IO3
set_location_assignment PIN_H13 -to flash_SCK
set_location_assignment PIN_H10 -to sd_DAT0_MISO
set_location_assignment PIN_J12 -to flash_IO0
set_location_assignment PIN_J13 -to sdram_DQ[15]
set_location_assignment PIN_K11 -to sdram_DQ[14]
set_location_assignment PIN_K13 -to serial_TXD
set_location_assignment PIN_K12 -to sdram_DQ[13]
set_location_assignment PIN_J10 -to sdram_DQ[8]
set_location_assignment PIN_L12 -to sdram_DQ[11]
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set_location_assignment PIN_L13 -to sdram_DQ[12]
set_location_assignment PIN_M13 -to sdram_DQ[10]
set_location_assignment PIN_L11 -to sdram_DQ[9]
set_location_assignment PIN_M12 -to sdram_UDQM
set_location_assignment PIN_N12 -to sdram_A[12]
set_location_assignment PIN_M11 -to sdram_A[8]
set_location_assignment PIN_N11 -to serial_RXD
set_location_assignment PIN_L10 -to sdram_A[5]
set_location_assignment PIN_H9 -to sdram_A[4]
set_location_assignment PIN_N10 -to sdram_A[7]
set_location_assignment PIN_J9 -to sdram_A[6]
set_location_assignment PIN_M10 -to sdram_CKE
set_location_assignment PIN_N9 -to sdram_BA[0]
set_location_assignment PIN_J8 -to sdram_A[9]
set_location_assignment PIN_H8 -to sdram_CLK
set_location_assignment PIN_M9 -to sdram_A[0]
set_location_assignment PIN_N8 -to sdram_A[3]
set_location_assignment PIN_M8 -to sdram_nCAS
set_location_assignment PIN_K7 -to sdram_A[1]
set_location_assignment PIN_K8 -to sdram_BA[1]
set_location_assignment PIN_N7 -to sdram_A[2]
set_location_assignment PIN_M7 -to sdram_A[10]
set_location_assignment PIN_N6 -to sdram_nCS
set_location_assignment PIN_J7 -to sdram_nWE
set_location_assignment PIN_K6 -to sdram_DQ[6]
set_location_assignment PIN_L5 -to sdram_nRAS
set_location_assignment PIN_N5 -to sdram_LDQM
set_location_assignment PIN_J6 -to sdram_DQ[2]
set_location_assignment PIN_M5 -to sdram_DQ[7]
set_location_assignment PIN_K5 -to sdram_DQ[1]
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set_location_assignment PIN_M4 -to sdram_DQ[4]
set_location_assignment PIN_J5 -to sdram_DQ[0]
set_location_assignment PIN_N3 -to sdram_DQ[3]
set_location_assignment PIN_M3 -to dac_dacdat
set_location_assignment PIN_N2 -to dac_lrclk
set_location_assignment PIN_L3 -to dac_mclk
set_location_assignment PIN_M2 -to dac_bclk
set_location_assignment PIN_M1 -to casIn
set_location_assignment PIN_L2 -to RST_n_in
set_location_assignment PIN_L1 -to dac_nmute
set_location_assignment PIN_L4 -to D_buf_nOE
set_location_assignment PIN_K1 -to data[7]
set_location_assignment PIN_K2 -to data[5]
set_location_assignment PIN_H5 -to data[4]
set_location_assignment PIN_J1 -to data[6]
set_location_assignment PIN_J2 -to data[3]
set_location_assignment PIN_H1 -to D_buf_DIR
set_location_assignment PIN_G4 -to data[2]
set_location_assignment PIN_H6 -to data[1]
set_location_assignment PIN_H4 -to clk_in
set_location_assignment PIN_H2 -to data[0]
set_location_assignment PIN_H3 -to RnW_in
set_location_assignment PIN_F1 -to kbd[3]
set_location_assignment PIN_G5 -to kbd[2]
set_location_assignment PIN_F4 -to NMI_n_in
set_location_assignment PIN_E1 -to IRQ_n_in
set_location_assignment PIN_E3 -to kbd[1]
set_location_assignment PIN_D1 -to input_buf_nOE
set_location_assignment PIN_E4 -to ROM_n
set_location_assignment PIN_C1 -to kbd[0]
set_location_assignment PIN_C2 -to addr[15]
set_location_assignment PIN_B1 -to addr[9]
set_location_assignment PIN_B2 -to addr[10]
set_location_assignment PIN_B9 -to mcu_MOSI
set_location_assignment PIN_D8 -to mcu_SCK
set_location_assignment PIN_E5 -to mcu_MISO
set_location_assignment PIN_D6 -to mcu_SS


set_instance_assignment -name WEAK_PULL_UP_RESISTOR ON -to mcu_SS
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
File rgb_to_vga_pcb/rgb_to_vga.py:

#!/usr/bin/python

# Copyright 2019 Google LLC
#
# Licensed under the Apache License, Version 2.0 (the "License");
# you may not use this file except in compliance with the License.
# You may obtain a copy of the License at
#
#     http://www.apache.org/licenses/LICENSE-2.0
#
# Unless required by applicable law or agreed to in writing, software
# distributed under the License is distributed on an "AS IS" BASIS,
# WITHOUT WARRANTIES OR CONDITIONS OF ANY KIND, either express or implied.
# See the License for the specific language governing permissions and
# limitations under the License.

# ---------------------
# rgb_to_vga
# ---------------------

# by Phillip Pearson

# A sync separator board, to allow connecting a VGA monitor to the RGB output
# of an Electron with the Ultimate Upgrade (http://myelin.nz/elkula).


# VGA devices expect 0-0.7V into 75 ohms on the R/G/B lines, i.e. they sink
# ~9.3mA at max brightness.  Ideally we would use a video buffer like a
# THS7316DR -- http://www.ti.com/lit/ds/symlink/ths7316.pdf -- which has the
# correct output impedance, but 5V CMOS with 460R in series, or 3.3V with 270R
# in series, will work.

# The CSYNC signal needs to be split into HSYNC and VSYNC; the EL1883 does
# this.  These are terminated in the display device with 2kR to +5V, so normal
# TTL outputs are OK; I've seen series termination of 82.5R used with 3.3V
# CMOS outputs.

# See VESA PND spec: http://web.archive.org/web/20030704041337/www.vesa.org/public/PnD/pnd.pdf


# Early Elks just passed the ULA pins directly out to the RGB socket; later
# ones buffer with a 74LS08 and 68R.  The Ultimate Upgrade buffers everything
# with a 74HCT245, so either you get a 5V CMOS signal, or a 74LS08 (~1250R
# output impedance) + 68R.

# In this case we're just handling 1-bit signals, so it should be sufficient
# to buffer R/G/B with a 74HCT125 then 480R.

# The EL1883 needs a video input between 0.5-2V p-p, so we buffer CSYNC then
# pass it through a 1:5 resistor divider to give a 1V signal.

# The EL1883's HSYNC and VSYNC outputs are not specified to be able to pull
# 2kR down to 0.5V, so we buffer those too.


PROJECT_NAME = "rgb_to_vga"


import sys, os
here = os.path.dirname(sys.argv[0])
sys.path.insert(0, os.path.join(here, "../pcb/myelin-kicad.pretty"))
import myelin_kicad_pcb
Pin = myelin_kicad_pcb.Pin


caps = [
    # bulk
    myelin_kicad_pcb.C0805("10u", "GND", "5V", ref="C1"),
    # 74HCT245
    myelin_kicad_pcb.C0805("100n", "GND", "5V", ref="C2"),
    # EL1883
    myelin_kicad_pcb.C0805("100n", "GND", "5V", ref="C3"),
    myelin_kicad_pcb.C0805("100n", "CS_divided", "CS_coupled", ref="C4"),
    myelin_kicad_pcb.C0805("100n", "RSET", "GND", ref="C5"),
]

resistors = [
    # Some very light termination on the inputs
    myelin_kicad_pcb.R0805("10k NF", "R_in", "GND", ref="R1"),
    myelin_kicad_pcb.R0805("10k NF", "G_in", "GND", ref="R2"),
    myelin_kicad_pcb.R0805("10k NF", "B_in", "GND", ref="R3"),
    myelin_kicad_pcb.R0805("10k NF", "CS_in", "GND", ref="R4"),
    # Divide buffered sync down for EL1883
    myelin_kicad_pcb.R0805("4k TBD", "CS_buf", "CS_divided", ref="R5"),
    myelin_kicad_pcb.R0805("1k TBD", "CS_divided", "GND", ref="R6"),  # TODO need 1:4 ratio, find better values
    # Output resistors for R/G/B (remote temination is 75R to GND)
    myelin_kicad_pcb.R0805("480R", "R_buf", "R_out", ref="R7"),
    myelin_kicad_pcb.R0805("480R", "G_buf", "G_out", ref="R8"),
    myelin_kicad_pcb.R0805("480R", "B_buf", "B_out", ref="R9"),
    # Output resistors for HS/VS (remote termination is 2kR to +5V)
    myelin_kicad_pcb.R0805("100R", "HS_buf", "HS_out", ref="R10"),
    myelin_kicad_pcb.R0805("100R", "VS_buf", "VS_out", ref="R11"),
    # RSET on EL1883
    myelin_kicad_pcb.R0805("681k 1%", "RSET", "GND", ref="R12"),
]

signal_buf = [
    myelin_kicad_pcb.Component(
        footprint="Package_SO:SSOP-20_4.4x6.5mm_P0.65mm",
        identifier=ident,
        value="74HCT245PW",
        desc="https://www.digikey.com/product-detail/en/nexperia-usa-inc/74HCT245PW118/1727-6353-1-ND",
        pins=[
            Pin( 1, "A->B", DIR),
            Pin( 2, "A0",   conn[0][0]),
            Pin( 3, "A1",   conn[1][0]),
            Pin( 4, "A2",   conn[2][0]),
            Pin( 5, "A3",   conn[3][0]),
            Pin( 6, "A4",   conn[4][0]),
            Pin( 7, "A5",   conn[5][0]),
            Pin( 8, "A6",   conn[6][0]),
            Pin( 9, "A7",   conn[7][0]),
            Pin(10, "GND",  "GND"),
            Pin(11, "B7",   conn[7][1]),
            Pin(12, "B6",   conn[6][1]),
            Pin(13, "B5",   conn[5][1]),
            Pin(14, "B4",   conn[4][1]),
            Pin(15, "B3",   conn[3][1]),
            Pin(16, "B2",   conn[2][1]),
            Pin(17, "B1",   conn[1][1]),
            Pin(18, "B0",   conn[0][1]),
            Pin(19, "nCE",  nOE),
            Pin(20, "VCC",  power),
        ],
    )
    for power, ident, DIR, nOE, conn in [
        (
            "5V",
            "BUF",
            "5V",  # DIR = A -> B
            "GND", # always active
            [
                # [A port, B port]
                ["R_in", "R_buf"],   # from input cable
                ["G_in", "G_buf"],   # from input cable
                ["B_in", "B_buf"],   # from input cable
                ["GND", ""],         # spare
                ["VS", "VS_buf"],    # from EL1883
                ["HS", "HS_buf"],    # from EL1883
                ["GND", ""],         # spare
                ["CS_in", "CS_buf"], # from input cable
            ]
        )
    ]
]

el1883 = [
    myelin_kicad_pcb.Component(
        # 8-SOIC (0.154", 3.90mm Width)
        footprint="Package_SO:SOIC-8_3.9x4.9mm_P1.27mm",
        identifier="SYNC",
        value="EL1883",
        pins=[
            Pin( 1, "CSYNC_out"),
            Pin( 2, "COMPOSITE_in",    "CS_coupled"),
            Pin( 3, "VSYNC_out",       "VS"),
            Pin( 4, "GND",             "GND"),
            Pin( 5, "BURST/PORCH_out"),
            Pin( 6, "RSET",            "RSET"),
            Pin( 7, "HSYNC_out",       "HS"),
            Pin( 8, "VDD",             "5V"),
        ],
    )
]

rgb_in =  [
    myelin_kicad_pcb.Component(
        footprint="Connector_PinHeader_2.54mm:PinHeader_1x06_P2.54mm_Vertical",
        identifier="RGB",
        value="RGB",
        pins=[
            Pin(1, "5V", "5V"),
            Pin(2, "GND", "GND"),
            Pin(3, "R", "R_in"),
            Pin(4, "G", "G_in"),
            Pin(5, "B", "B_in"),
            Pin(6, "CS", "CS_in"),
        ],
    )
]

vga_out = [
    myelin_kicad_pcb.Component(
        footprint="Connector_Dsub:DSUB-15-HD_Female_Horizontal_P2.29x1.98mm_EdgePinOffset3.03mm_Housed_MountingHolesOffset4.94mm",
        identifier="VGA",
        value="VGA",
        pins=[
            Pin( 1, "R", "R_out"),
            Pin( 2, "G", "G_out"),
            Pin( 3, "B", "B_out"),
            Pin( 4, "ID2/RES"),
            Pin( 5, "HS_GND", "GND"),
            Pin( 6, "RED_RTN", "GND"),
            Pin( 7, "GREEN_RTN", "GND"),
            Pin( 8, "BLUE_RTN", "GND"),
            Pin( 9, "KEY/PWR"),
            Pin(10, "VS_GND", "GND"),
            Pin(11, "ID0/RES"),
            Pin(12, "ID1/SDA"),
            Pin(13, "HS", "HS_out"),
            Pin(14, "VS", "VS_out"),
            Pin(15, "ID3/SCL"),
        ],
    )
]

myelin_kicad_pcb.dump_netlist("%s.net" % PROJECT_NAME)
myelin_kicad_pcb.dump_bom("bill_of_materials.txt",
                          "readable_bill_of_materials.txt")

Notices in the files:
altera/ElectronULA_max10.qsf:
Copyright (C) 1991-2013 Altera Corporation
pcb/max10_electron_ula.py:
This source file is free software: you can redistribute it and/or modify
it under the terms of the GNU General Public License as published
